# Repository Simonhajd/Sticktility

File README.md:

Stick-Tility (Stick Utility)

## About the Project / What it is:

Stick-Tility is a  handheld device that powers and reads data from snap-on sensor modules. Once a sensor is connected, it can record data at set time intervals and graph the data on its screen. It can charge via the USB-C on the side, and the KB2040 Microcontroller can be updated or connected to a computer using the same USB-C port. This all fits in a durable case smaller than a TV remote.

### Use cases:
* UV exposure logger
* * For example, you could easily set it up to record and display the current UV level and notify you when it reaches a certain threshold. Then you could just swap the UV sensor with a VOC sensor and it would instantly show you data about your air quality.
* Gps recorder for activities
* Analyzing trends in weather
* VOC warning system
* Distance measuring tool
* Noise level safety warning
  
## My process:
When I was thinking of a project to create for Highway, I started by constraining myself to one of these four categories: Tools, Displays, Devices, and Interfaces. I chose to make a tool because I wanted something I could actually use. I decided on making the most compact tool I could. I came up with a few more contraints (handheld, battery powered), and started developing the tool. 

### Why:

I want to be able to use sensors more easily without wiring or breadboards. Stick-Tility removes the bulky computer and battery aspect of each individual tool and sensor, so you can simply snap on the sensor (with pogo pins, like a MacBook charger), and you will receive data. This means, for each sensor you would like to use, you just need the sensor (with i2c), and you just plug it in using a pogo system. One battery for everything. I wanted to build this since I loved the concept of a hot-swappable sensor device for whatever you'd like, that fits in your hand, with a hot-swappable sensor end which snaps on using just magnets and pins. 

## Case design process:

I designed the case to be easily taken apart for debugging/removal while still sitting solidly together. I came up with the concept of two "skeleton" parts I can slide over the PCB and battery to keep them in place, and a shell which I can slide the electronics into. after many tens of hours of work on the case, I came up with a design that should be very robust, as small as possible, and easy to use. I also have magnets to attach the additional components, and to snap the skeletons into the shell.

I created an explosion video of the model too to visualize the parts required on the build:

https://github.com/user-attachments/assets/41e0f8f3-01ee-4bec-a7f7-713455e94a45

### Past projects: 
The only PCB work I’ve done before is a single-layer PCB macropad. https://github.com/Simonhajd/Macropad. Ive done some cad practice but no projects. This was mostly the first time ive really challenged myself with CAD. Other than these, I have only done software/online work.

### Why this is worth 10 points: 
This isnt just a data reading device, this is a dynamic tool which can be easily programmed to compile data and visualize it, or record data over time. the device is allowed to be placed anywhere, start a recording, and log data every x hours. This product has the ability to be a part of a much larger ecosystem of tools and sensors. The intricate build of this case allows anything to be modularly swapped, and nothing is glued. There are so many parts which fit so seamlessly together to become one rigid device. Just two screws are used, and everything is held together by other objects, or magnets. The PCB contains two off-the-shelf boards, and many other features to optimize reliability and quality. Such as decoupling capacitors, data line tuning, and much more. And finally, roughly 67 hours were spent on this project.

### Total Hours spent: 66 Hours 33 Minutes

### Total price: $158.44

## BOM:

| Qty | Part | P/N | Supplier | Price | Link | Shipping + Tariffs | Tax | Total |
|-----|------|-----|----------|-------|------|---------------------|-----|-------|
| 1 | Adafruit PowerBoost 1000 Charger - Rechargeable 5V Lipo USB Boost @ 1A - 1000C | N/A | Adafruit | 19.95 | [Link](https://www.adafruit.com/product/2465) | 1.72 | 2.167 | 23.837 |
| 1 | On-Off Power Button / Pushbutton Toggle Switch | 1683 | Adafruit | 1.95 | [Link](https://www.adafruit.com/product/1683?gQT=1) | 1.92 | 0.387 | 4.257 |
| 1 | Adafruit KB2040 | 5302 | Adafruit | 8.95 | [Link](https://www.adafruit.com/product/5302) | 1.92 | 1.087 | 0 (own) |
| 1 | 2A Waterproof Magnetic Pogo Pin Connector (Male/Female) | N/A | Aliexpress | 13.38 | [Link](https://www.aliexpress.us/item/3256808648425959.html) | 0 | 1.338 | 14.718 |
| 1 | Gravity: GNSS GPS BeiDou Positioning Module with RTC - I2C&UART | DFR1103 | DFRobot | 17.9 | [Link](https://www.dfrobot.com/product-2815.html) | 15 | 3.29 | 36.19 |
| 1 | 128x64 OLED - SSD1306 - I2C | WEA012864DWPP3N00003 | Digikey | 9.53 | [Link](https://www.digikey.com/en/products/detail/winstar-display/WEA012864DWPP3N00003/20533255) | 1.208 | 1.0738 | 11.8118 |
| 1 | Decoupling Capacitor | C0402C104K9RACTU | Digikey | 0.1 | [Link](https://www.digikey.com/en/products/detail/kemet/c0402c104k9ractu/1090777) | 1.208 | 0.1308 | 1.4388 |
| 2 | 5.1kΩ Resistors | RC0603FR-075K1L | Digikey | 0.1 | [Link](https://www.digikey.com/en/products/detail/yageo/RC0603FR-075K1L/727268?s=N4IgTCBcDaIEoGEAMA2JBmAYnAtEg7AKwDSAjADIgC6AvkA) | 1.208 | 0.1308 | 1.4388 |
| 11 | 1mΩ Resistors | TLR3AWDTE2L00F | Digikey | 1.53 | [Link](https://www.digikey.com/en/products/detail/koa-speer-electronics-inc/tlr3awdte2l00f/9845546) | 1.208 | 0.2738 | 3.0118 |
| 1 | USB-C Connector | UJ31-CH-G-SMT-TR-67 | Digikey | 3.52 | [Link](https://www.digikey.com/en/products/detail/same-sky-formerly-cui-devices/UJ31-CH-G-SMT-TR-67/12702600) | 1.208 | 0.4728 | 5.2008 |
| 100 | Screw x2 | 90128A187 | McMaster-Carr | 8.41 | [Link](https://www.mcmaster.com/catalog/131/3561/90128A187) | 3.61 | 1.202 | 0 (own) |
| 1 | 2.40mm M3 Hex Nut x2 | 90591A250 | McMaster-Carr | 2.81 | [Link](https://www.mcmaster.com/catalog/131/3648/90591A250) | 3.61 | 0.642 | 0 (own) |
| 8 | Magnets (Disc OD 0.197) | 5902K47 | McMaster-Carr | 1.09 | [Link](https://www.mcmaster.com/products/magnets/magnets-2~/shape~disc/od~0-197/) | 3.61 | 0.47 | 5.17 |
| 1 | Adafruit Lithium Ion Cylindrical Battery - 3.7V 2200mAh | 1781 | Adafruit | 9.95 | [Link](https://www.adafruit.com/product/1781) | 1.92 | 1.187 | 13.057 |
| 1 | Sparkfun Multi-Directional Switch 5 Position - D-Pad (SMD) | COM-26850 | Sparkfun | 0.95 | [Link](https://www.sparkfun.com/multi-directional-switch-5-position-d-pad-smd.html) | 2.825 | 0.3775 | 4.1525 |
| 1 | Flexible Qwiic Cable - 200mm | PRT-17258 | Sparkfun | 1.95 | [Link](https://www.sparkfun.com/flexible-qwiic-cable-200mm.html) | 2.825 | 0.4775 | 5.2525 |
| 1 | Qwiic Cable - 100mm (cut in half) | PRT-14427 | Sparkfun | 1.5 | [Link](https://www.sparkfun.com/qwiic-cable-100mm.html) | 2.825 | 0.4325 | 4.7575 |
| 1 | SparkFun Micro Temperature Sensor | STTS22H | Sparkfun | 8.53 | [Link](https://www.sparkfun.com/sparkfun-micro-temperature-sensor-stts22h-qwiic.html) | 2.825 | 1.1355 | 12.4905 |
| 1 | PCB | N/A | JLCPCB | 2.1 | PCB in repo | 8.5 | 1.06 | 11.66 |

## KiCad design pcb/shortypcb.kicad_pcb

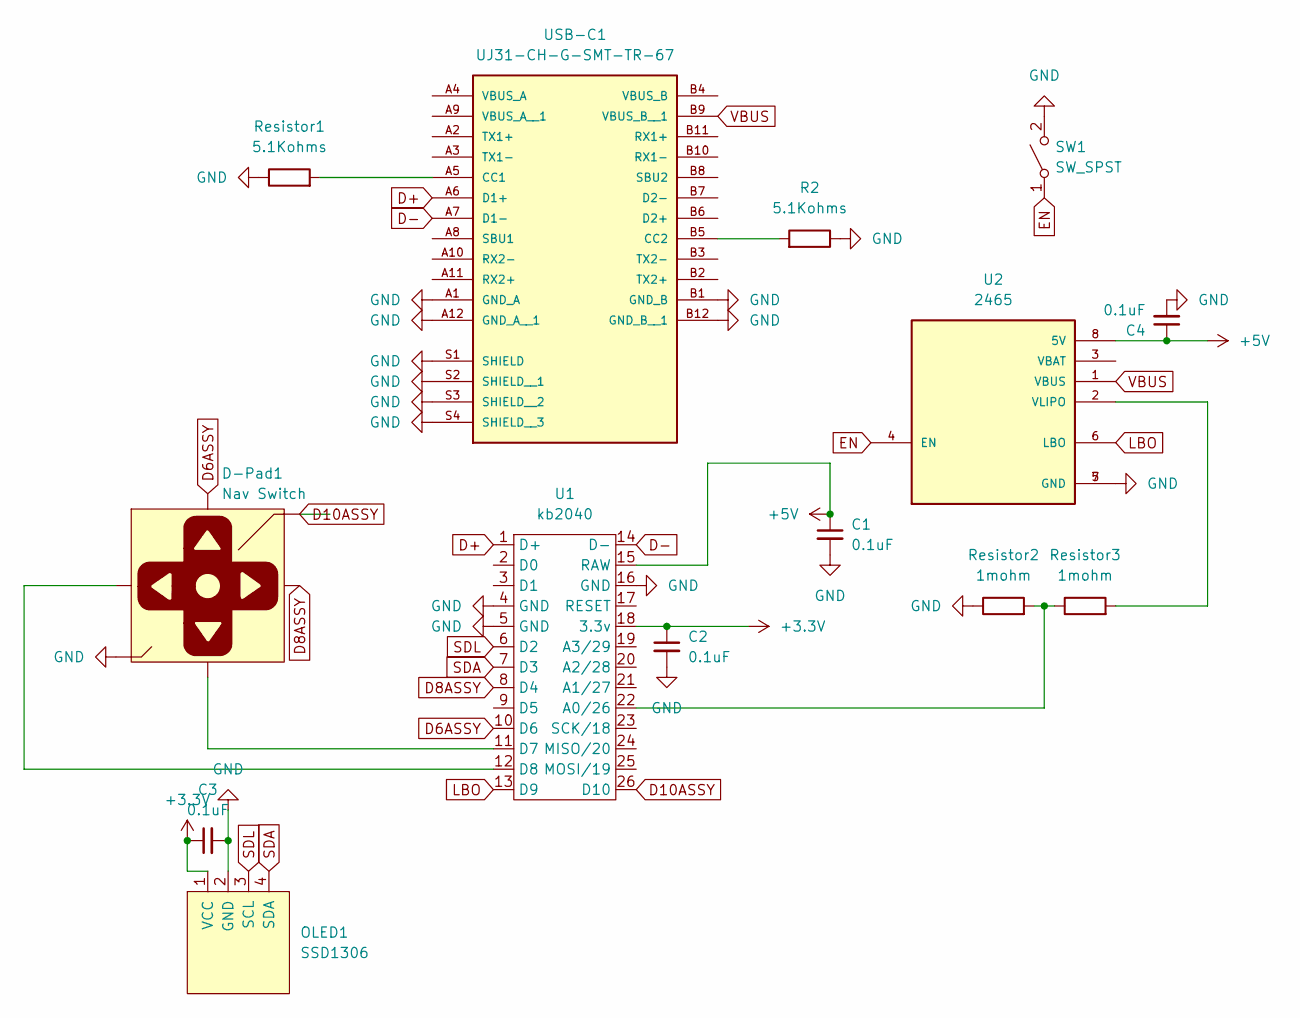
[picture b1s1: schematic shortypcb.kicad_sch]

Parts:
C1, C2, C3, C4: 0.1uF; CAPC1005X60
D-Pad1: Nav Switch; Navigation_SMD_9.9x9.9mm
OLED1: SSD1306; PinHeader_1x04_P2.00mm_Vertical
R2: 5.1Kohms; R_0603_1608Metric_Pad0.98x0.95mm_HandSolder
Resistor1: 5.1Kohms; RC0603N_YAG
Resistor2, Resistor3: 1mohm; RES_TLR_3AW1_2_4_KOA
SW1: SW_SPST; onoffswitch
U1: kb2040
U2: 2465; MODULE_2465; PARTREV B
USB-C1: UJ31-CH-G-SMT-TR-67; CUI_UJ31-CH-G-SMT-TR-67; PARTREV 1.0

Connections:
+3.3V: C2.1, C3.1, OLED1.1 (VCC), U1.18 (3.3v); also elsewhere on the board
+5V: C1.1, C4.1, U1.15 (RAW), U2.8 (5V)
D6ASSY: D-Pad1.1 (Up), U1.10 (D6)
D8ASSY: D-Pad1.2 (Right), U1.8 (D4)
D10ASSY: D-Pad1.4 (Center), U1.26 (D10)
D+: U1.1 (D+), USB-C1.A6 (D1+)
D-: U1.14 (D-), USB-C1.A7 (D1-)
EN: SW1.1 (A), U2.4 (EN)
GND: C1.2, C2.2, C3.2, C4.2, D-Pad1.3 (GND), D-Pad1.6 (GND), D-Pad1.8 (GND), D-Pad1.9 (GND), D-Pad1.10 (GND), OLED1.2 (GND), R2.1, Resistor1.1, Resistor2.1, SW1.2 (B), U1.4 (GND), U1.5 (GND), U1.16 (GND), U2.5 (GND), U2.7 (GND), USB-C1.A1 (GND_A), USB-C1.A12 (GND_A__1), USB-C1.B1 (GND_B), USB-C1.B12 (GND_B__1), USB-C1.S1 (SHIELD), USB-C1.S2 (SHIELD__1), USB-C1.S3 (SHIELD__2), USB-C1.S4 (SHIELD__3); also elsewhere on the board
LBO: U1.13 (D9), U2.6 (LBO)
unnamed: Resistor2.2, Resistor3.1, U1.22 (A0/26)
unnamed: D-Pad1.5 (Down), U1.11 (D7)
unnamed: D-Pad1.7 (Left), U1.12 (D8)
unnamed: Resistor3.2, U2.2 (VLIPO)
unnamed: Resistor1.2, USB-C1.A5 (CC1)
unnamed: R2.2, USB-C1.B5 (CC2)
SDA: OLED1.4 (SDA), U1.7 (D3); also elsewhere on the board
SDL: OLED1.3 (SCL), U1.6 (D2); also elsewhere on the board
VBUS: U2.1 (VBUS), USB-C1.B9 (VBUS_B__1)

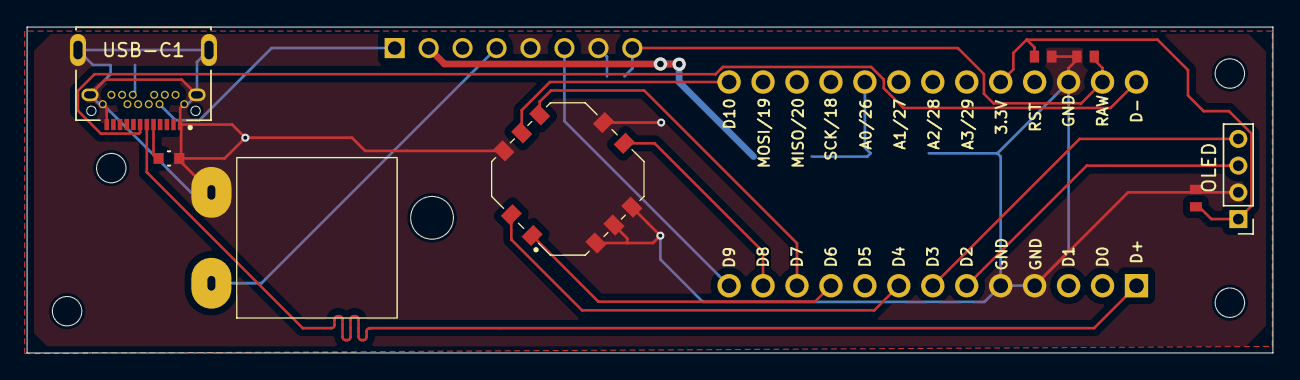
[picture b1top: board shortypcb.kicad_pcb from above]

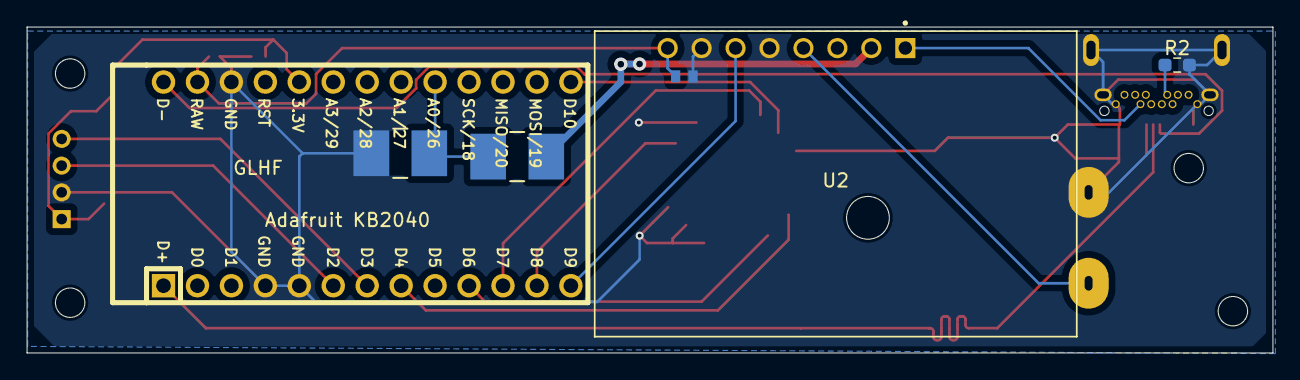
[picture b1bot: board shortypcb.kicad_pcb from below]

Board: 2 copper layers, 93.2 x 24.4 mm, 14 parts (6 on the bottom side), 19 nets.

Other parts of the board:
OLED: SSD1306; PinHeader_1x04_P2.00mm_Vertical

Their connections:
+3.3V: OLED.1 (VCC); also elsewhere on the board
GND: OLED.2 (GND); also elsewhere on the board
SDA: OLED.4 (SDA); also elsewhere on the board
SDL: OLED.3 (SCL); also elsewhere on the board

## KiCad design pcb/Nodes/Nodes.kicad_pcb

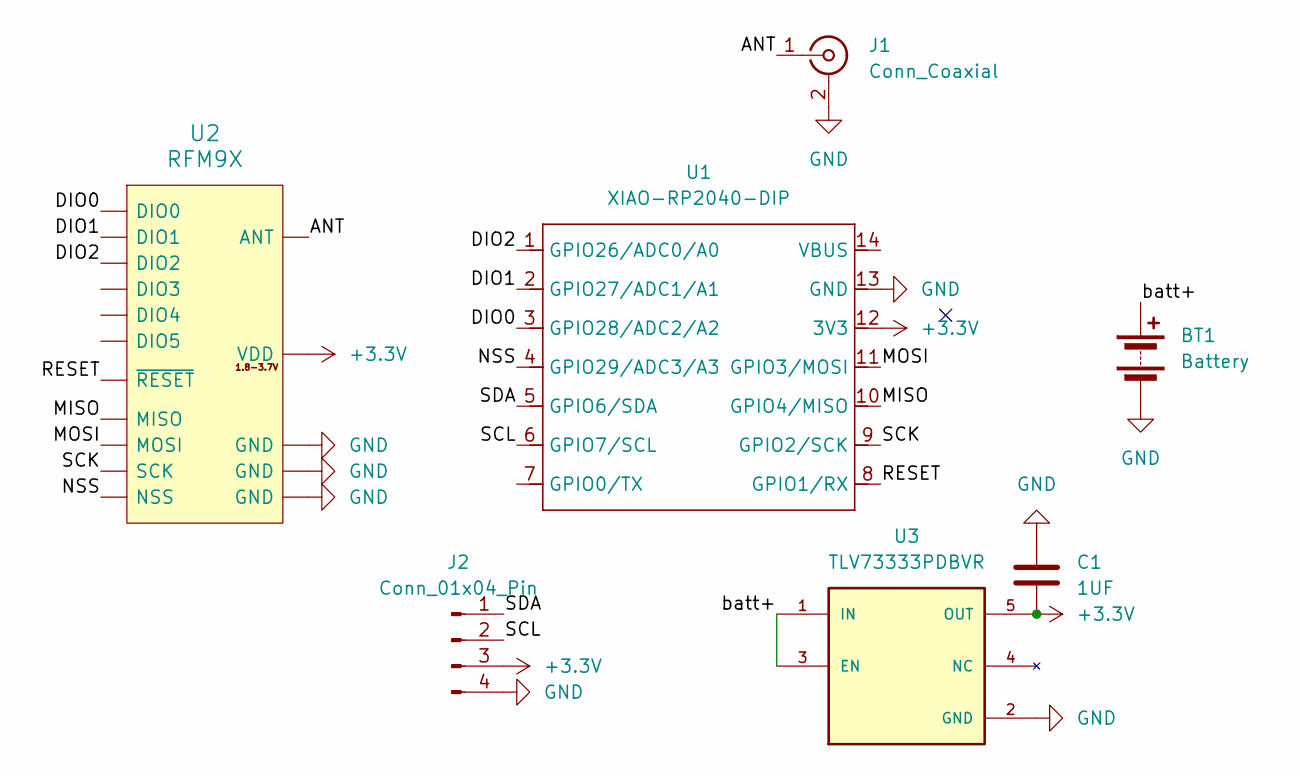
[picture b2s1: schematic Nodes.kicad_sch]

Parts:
BT1: Battery; BAT_BA1AAPC
C1: 1UF; CAPC1005X60
J1: Conn_Coaxial; CONN_PCB.SMAFRA_TAL
J2: Conn_01x04_Pin; pads
U1: XIAO-RP2040-DIP
U2: RFM9X; HOPERF_RFM9XW_SMD
U3: TLV73333PDBVR; SOT95P280X145-5N; PARTREV C

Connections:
+3.3V: C1.2, J2.3, U1.12 (3V3), U2.12 (VDD), U3.5 (OUT)
/ANT: J1.1 (In), U2.16 (ANT)
/DIO0: U1.3 (GPIO28/ADC2/A2), U2.11 (DIO0)
/DIO1: U1.2 (GPIO27/ADC1/A1), U2.10 (DIO1)
/DIO2: U1.1 (GPIO26/ADC0/A0), U2.9 (DIO2)
/MISO: U1.10 (GPIO4/MISO), U2.2 (MISO)
/MOSI: U1.11 (GPIO3/MOSI), U2.3 (MOSI)
/NSS: U1.4 (GPIO29/ADC3/A3), U2.5 (NSS)
/RESET: U1.8 (GPIO1/RX), U2.6 (~RESET)
/SCK: U1.9 (GPIO2/SCK), U2.4 (SCK)
/SCL: J2.2, U1.6 (GPIO7/SCL)
/SDA: J2.1, U1.5 (GPIO6/SDA)
/batt+: BT1.1 (+), U3.1 (IN), U3.3 (EN)
GND: BT1.2 (-), C1.1, J1.2 (Ext), J2.4, U1.13 (GND), U2.1 (GND), U2.8 (GND), U2.15 (GND), U3.2 (GND)

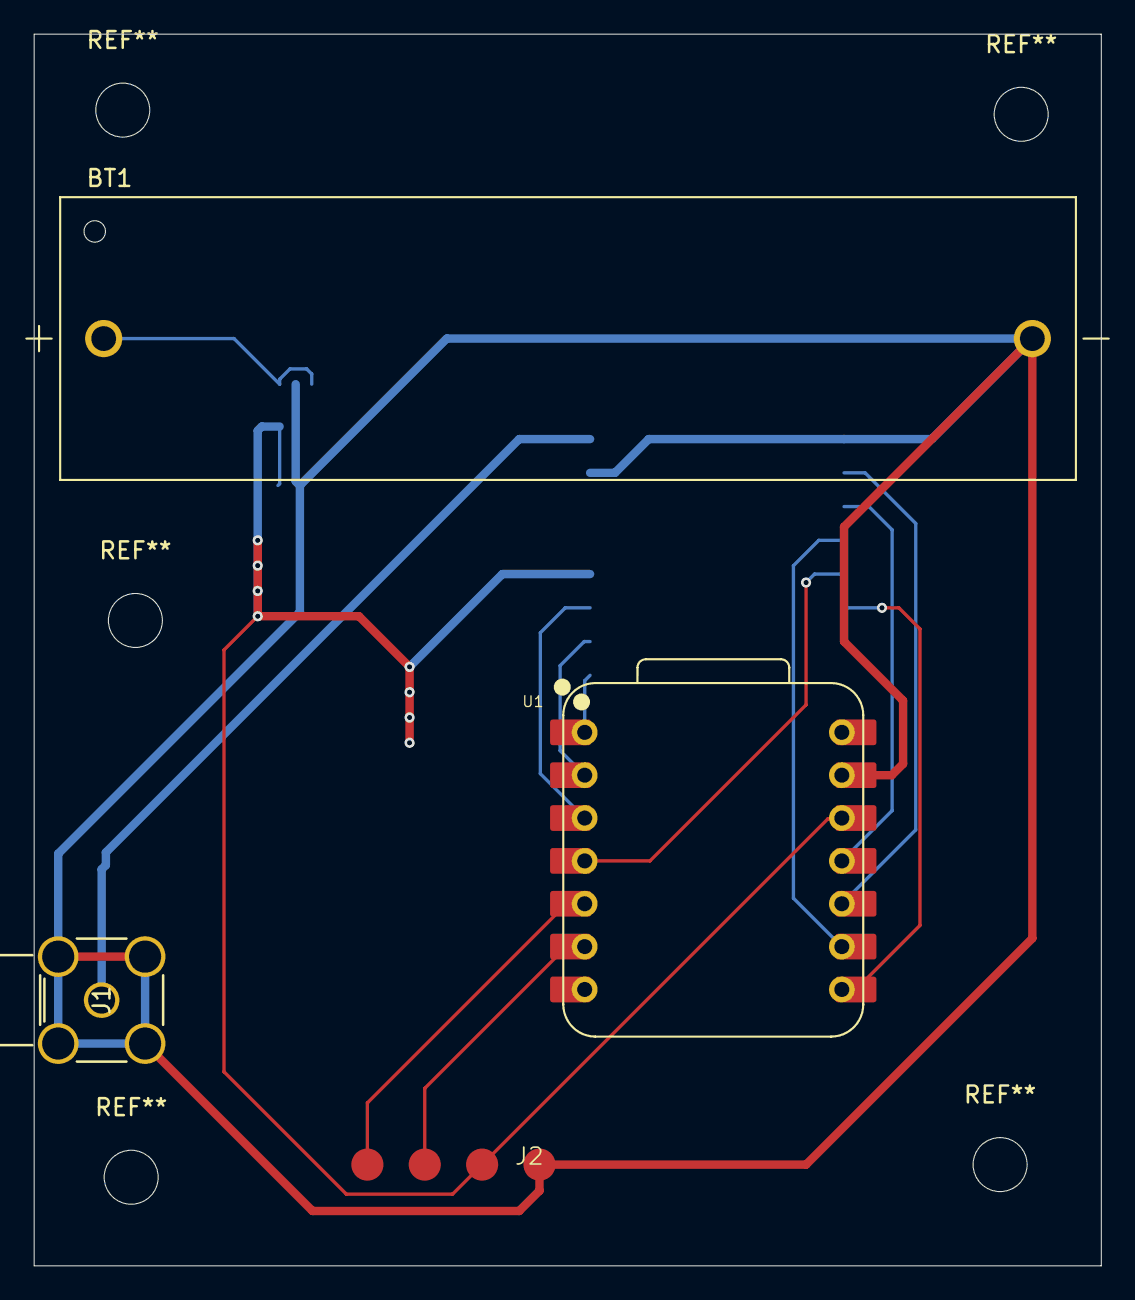
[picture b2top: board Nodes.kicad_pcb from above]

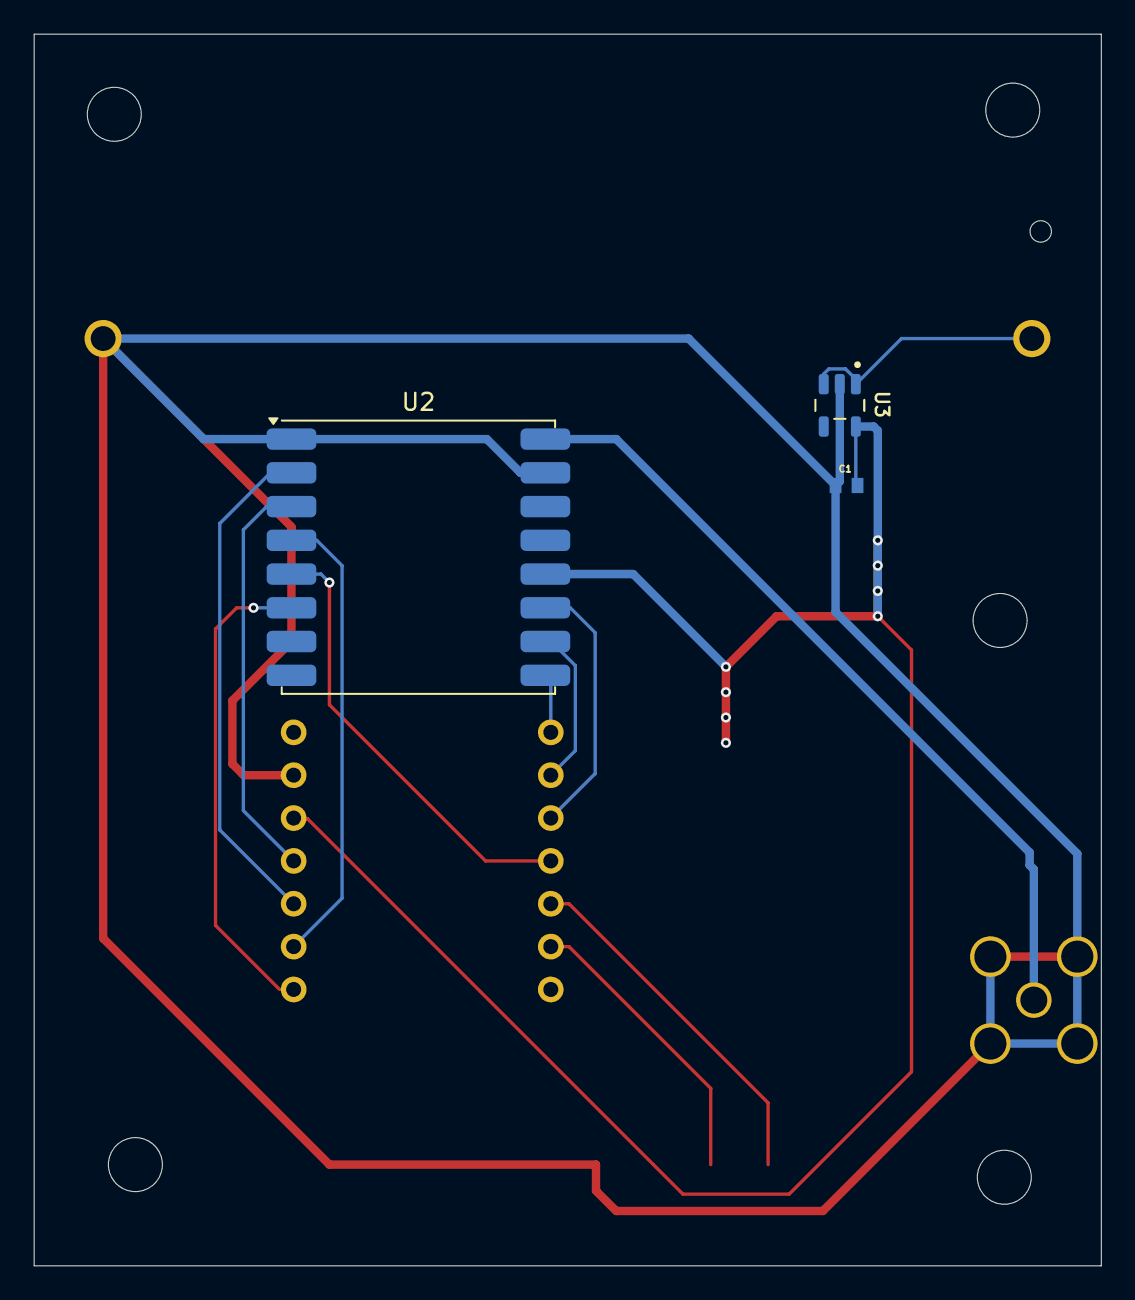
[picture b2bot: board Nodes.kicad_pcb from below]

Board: 2 copper layers, 63.2 x 73.0 mm, 7 parts (3 on the bottom side), 14 nets.

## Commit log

2025-05-26 Publish Commit
2025-05-26 added bas to readme
2025-05-28 PCB work
    pcb work - didnt commit the symbols and schematics since there not mine- dont wanna do something wrong
2025-05-29 Changed the filesystem+simplified. worked a lot on the pcb design.too
2025-05-29 gotta redo the board brahhh - the oled cant fit in the current orientation.
2025-05-30 I messed around with the wiring more - now it should be done. need to do some final checks before sent off (whatever that means)
2025-05-31 Maybe finished the board? looks good to me. gonna look it over with others first
2025-05-31 Journal commit (forgot to commit this :( )
2025-05-31 added pics
2025-05-31 just a push to move stuff to my pc
2025-05-31 Refreshed th eoled design to accomodate the screen i found - swapped vcc and gnd
2025-05-31 made the 3d model to pre for case design
2025-06-12 made the pcb a lot shorter- forgot to push
2025-06-12 added crazy amounts of files to gitignore
2025-06-12 journal push
2025-06-12 journal refresh push
2025-06-12 fixed gremmer
2025-06-12 my step file for the project - finally figured it out
2025-06-13 addded the nodes concept. 7 hour day
2025-06-14 Node work + GNSS concept
2025-06-14 GNSS module build.
2025-06-14 Node concept i probably wont use.
2025-06-14 taotl time
2025-06-15 uhh update june fourteeth
2025-06-16 PCB is done?
2025-06-21 BOM BOM WOW WOW
2025-06-21 Rename BOM.txt to BOM-IGNORE.txt
2025-06-21 pcb updates - new resistors and slight layout work
2025-06-22 made the ino code for the kb2040
2025-06-22 gitignore
2025-06-22 Moved the 3d models into its own folder
2025-06-22 new folder for code
2025-06-26 more pictures should be good
